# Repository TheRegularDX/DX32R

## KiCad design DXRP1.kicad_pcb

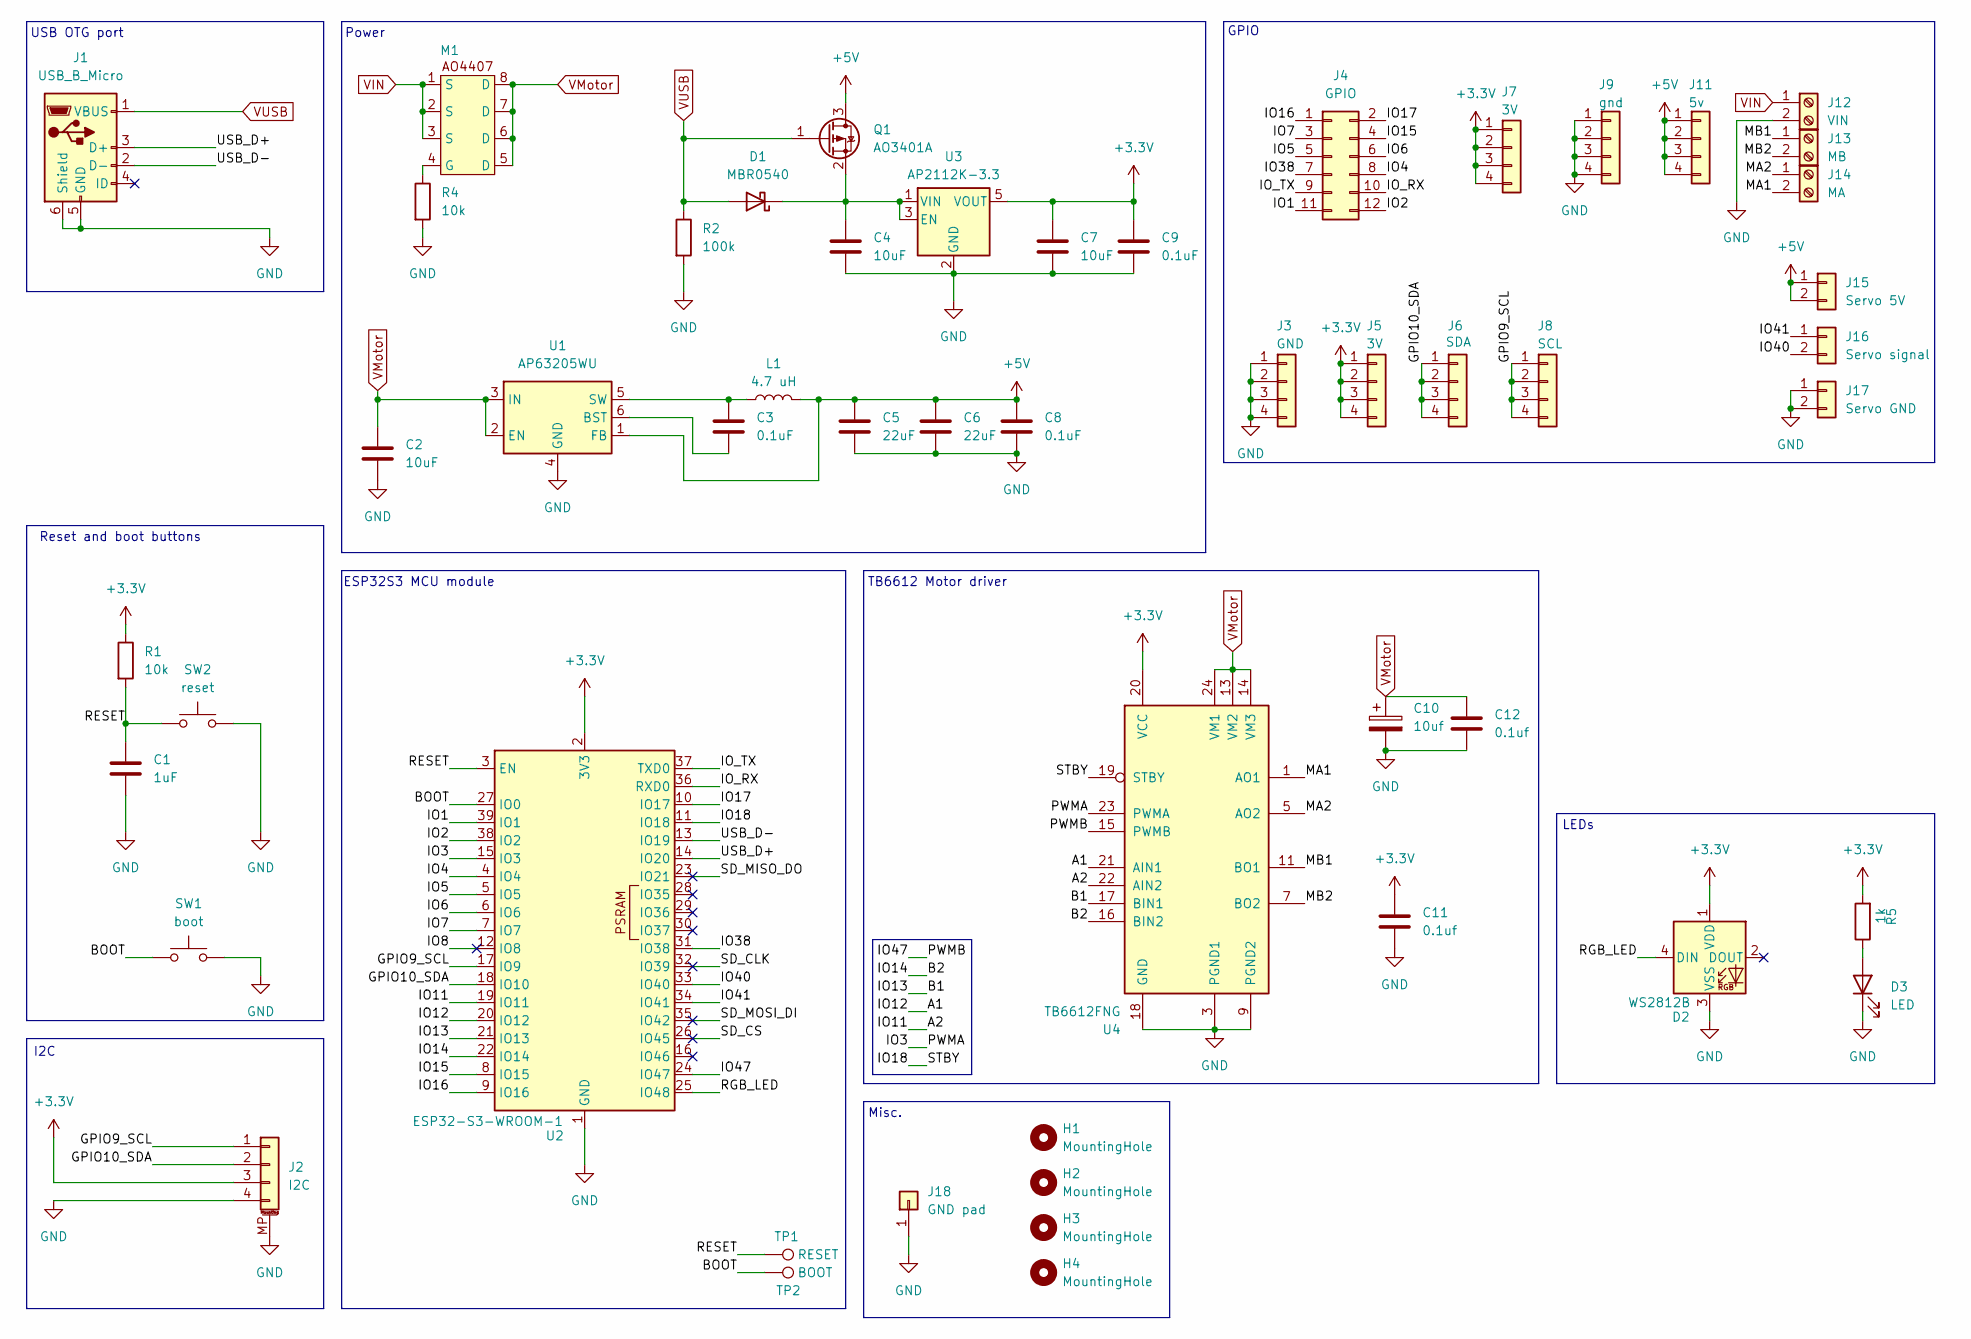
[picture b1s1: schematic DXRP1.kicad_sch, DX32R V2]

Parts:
C1: 1uF; C_0805_2012Metric_Pad1.18x1.45mm_HandSolder
C2, C4, C7: 10uF; C_0805_2012Metric_Pad1.18x1.45mm_HandSolder
C3, C8, C9: 0.1uF; C_0603_1608Metric_Pad1.08x0.95mm_HandSolder
C5, C6: 22uF; C_0805_2012Metric_Pad1.18x1.45mm_HandSolder
C10: 10uf; C_1206_3216Metric
C11, C12: 0.1uf; C_0603_1608Metric_Pad1.08x0.95mm_HandSolder
D1: MBR0540; D_SOD-123
D2: WS2812B; LED_WS2812B_PLCC4_5.0x5.0mm_P3.2mm
D3: LED; LED_0805_2012Metric_Pad1.15x1.40mm_HandSolder
H1, H2, H3, H4: MountingHole; MountingHole_3.2mm_M3_DIN965
J1: USB_B_Micro; USB_Micro-B_Molex-105017-0001
J2: I2C; JST_SH_BM04B-SRSS-TB_1x04-1MP_P1.00mm_Vertical
J3: GND; PinHeader_1x04_P2.54mm_Vertical_Custom
J4: GPIO; PinHeader_2x06_P2.54mm_Vertical_Custom
J5, J7: 3V; PinHeader_1x04_P2.54mm_Vertical_Custom
J6: SDA; PinHeader_1x04_P2.54mm_Vertical_Custom
J8: SCL; PinHeader_1x04_P2.54mm_Vertical_Custom
J9: gnd; PinHeader_1x04_P2.54mm_Vertical_Custom
J11: 5v; PinHeader_1x04_P2.54mm_Vertical_Custom
J12: VIN; TerminalBlock_MetzConnect_Type055_RT01502HDWU_1x02_P5.00mm_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
J13: MB; TerminalBlock_MetzConnect_Type055_RT01502HDWU_1x02_P5.00mm_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
J14: MA; TerminalBlock_MetzConnect_Type055_RT01502HDWU_1x02_P5.00mm_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
J15: Servo 5V; PinHeader_1x02_P2.54mm_Vertical
J16: Servo signal; PinHeader_1x02_P2.54mm_Vertical_Custom
J17: Servo GND; PinHeader_1x02_P2.54mm_Vertical_Custom
J18: GND pad; PinSocket_1x01_P2.54mm_Vertical
L1: 4.7 uH; L_Chilisin_BMRA00040420
M1: SO-8_3.9x4.9mm_P1.27mm
Q1: AO3401A; SOT-23
R1: 10k; R_0603_1608Metric_Pad0.98x0.95mm_HandSolder
R2: 100k; R_0603_1608Metric_Pad0.98x0.95mm_HandSolder
R4: 10k; R_0805_2012Metric_Pad1.20x1.40mm_HandSolder
R5: 1k; R_0805_2012Metric_Pad1.20x1.40mm_HandSolder
SW1: boot; SW_Push_SPST_NO_Alps_SKRK
SW2: reset; SW_Push_SPST_NO_Alps_SKRK
TP1: RESET; TestPoint_Pad_D1.5mm
TP2: BOOT; TestPoint_Pad_D1.5mm
U1: AP63205WU; TSOT-23-6
U2: ESP32-S3-WROOM-1
U3: AP2112K-3.3; SOT-23-5
U4: TB6612FNG; SSOP-24_5.3x8.2mm_P0.65mm

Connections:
+3.3V: C7.1, C9.1, C11.1, D2.1 (VDD), J2.3, J5.1, J5.2, J5.3, J5.4, J7.1, J7.2, J7.3, J7.4, R1.1, R5.2, U2.2 (3V3), U3.5 (VOUT), U4.20 (VCC)
+5V: C5.1, C6.1, C8.1, J11.1, J11.2, J11.3, J11.4, J15.1, J15.2, L1.2, Q1.3 (D), U1.1 (FB)
/A1: U2.20 (IO12), U4.21 (AIN1)
/A2: U2.19 (IO11), U4.22 (AIN2)
/B1: U2.21 (IO13), U4.17 (BIN1)
/B2: U2.22 (IO14), U4.16 (BIN2)
/BOOT: SW1.1, TP2.1, U2.27 (IO0)
/GPIO9_SCL: J2.1, J8.1, J8.2, J8.3, J8.4, U2.17 (IO9)
/GPIO10_SDA: J2.2, J6.1, J6.2, J6.3, J6.4, U2.18 (IO10)
/IO1: J4.11, U2.39 (IO1)
/IO2: J4.12, U2.38 (IO2)
/IO3: U2.15 (IO3), U4.23 (PWMA)
/IO4: J4.8, U2.4 (IO4)
/IO5: J4.5, U2.5 (IO5)
/IO6: J4.6, U2.6 (IO6)
/IO7: J4.3, U2.7 (IO7)
/IO8: U2.12 (IO8)
/IO15: J4.4, U2.8 (IO15)
/IO16: J4.1, U2.9 (IO16)
/IO17: J4.2, U2.10 (IO17)
/IO18: U2.11 (IO18), U4.19 (STBY)
/IO38: J4.7, U2.31 (IO38)
/IO40: J16.2, U2.33 (IO40)
/IO41: J16.1, U2.34 (IO41)
/IO47: U2.24 (IO47), U4.15 (PWMB)
/IO_RX: J4.10, U2.36 (RXD0)
/IO_TX: J4.9, U2.37 (TXD0)
/MA1: J14.2, U4.1 (AO1), U4.2 (AO1)
/MA2: J14.1, U4.5 (AO2), U4.6 (AO2)
/MB1: J13.1, U4.11 (BO1), U4.12 (BO1)
/MB2: J13.2, U4.7 (BO2), U4.8 (BO2)
/RESET: C1.1, R1.2, SW2.1, TP1.1, U2.3 (EN)
/RGB_LED: D2.4 (DIN), U2.25 (IO48)
/SD_CLK: U2.32 (IO39)
/SD_CS: U2.26 (IO45)
/SD_MISO_DO: U2.23 (IO21)
/SD_MOSI_DI: U2.35 (IO42)
/USB_D+: J1.3 (D+), U2.14 (IO20)
/USB_D-: J1.2 (D-), U2.13 (IO19)
GND: C1.2, C2.2, C4.2, C5.2, C6.2, C7.2, C8.2, C9.2, C10.2, C11.2, C12.2, D2.3 (VSS), D3.1 (K), J1.5 (GND), J1.6 (Shield), J2.4, J2.MP (MountPin), J3.1, J3.2, J3.3, J3.4, J9.1, J9.2, J9.3, J9.4, J12.2, J17.1, J17.2, J18.1, R2.2, R4.2, SW1.2, SW2.2, U1.4 (GND), U2.1 (GND), U2.40 (GND), U2.41 (GND), U3.2 (GND), U4.3 (PGND1), U4.4 (PGND1), U4.9 (PGND2), U4.10 (PGND2), U4.18 (GND)
unnamed: C4.1, D1.1 (K), Q1.2 (S), U3.1 (VIN), U3.3 (EN)
unnamed: D3.2 (A), R5.1
unnamed: M1.4 (G), R4.1
unnamed: C3.2, U1.6 (BST)
unnamed: C3.1, L1.1, U1.5 (SW)
VIN: J12.1, M1.1 (S), M1.2 (S), M1.3 (S)
VMotor: C2.1, C10.1, C12.1, M1.5 (D), M1.6 (D), M1.7 (D), M1.8 (D), U1.2 (EN), U1.3 (IN), U4.13 (VM2), U4.14 (VM3), U4.24 (VM1)
VUSB: D1.2 (A), J1.1 (VBUS), Q1.1 (G), R2.1

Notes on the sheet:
GPIO
I2C
TB6612 Motor driver
ESP32S3 MCU module
Power
Misc.
USB OTG port
LEDs
Reset and boot buttons

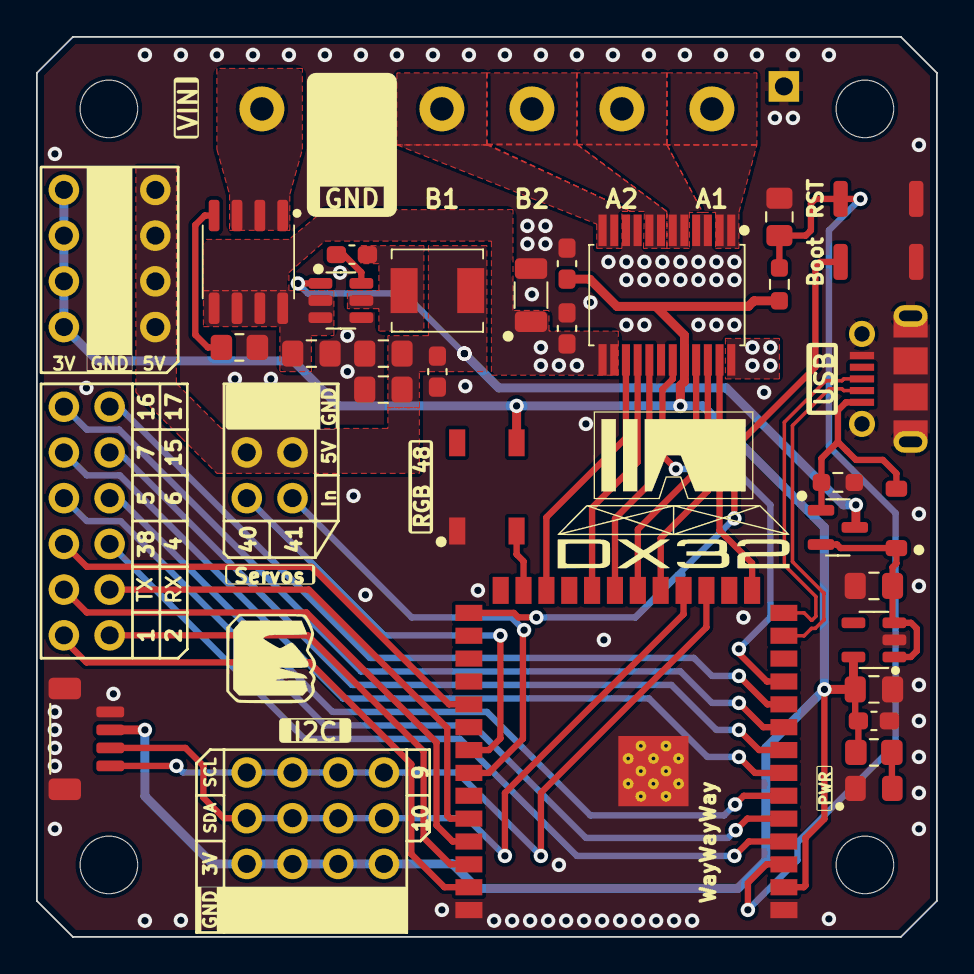
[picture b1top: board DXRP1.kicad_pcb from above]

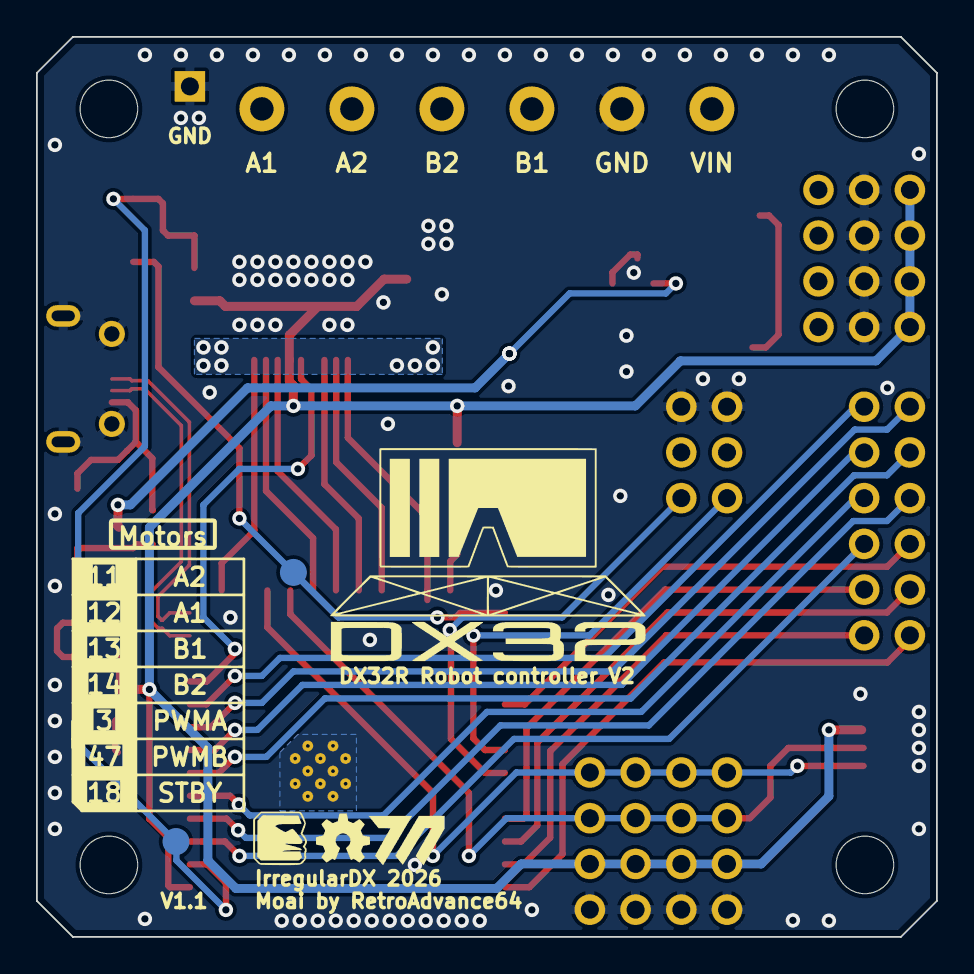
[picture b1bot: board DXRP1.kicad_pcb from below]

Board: 2 copper layers, 50.0 x 50.0 mm, 51 parts (2 on the bottom side), 43 nets.

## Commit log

2026-06-23 Rename 20260620_171710.jpg to DX32R.jpg
2026-06-24 Revision 1.1
    Added proper USB backpowering protection circuit
